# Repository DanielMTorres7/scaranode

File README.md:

# ScaraNode

Placa de nó de motor **Klipper** para braço SCARA: **RP2040-Zero** + **TMC2209** (NEMA 17) e/ou driver
externo **DM556** (NEMA 23), cada um com STEP/DIR/enable próprios. Face única, 76 × 64 mm, feita para fresar em casa.

| Projetista | Revisão | Data | Estado |
|---|---|---|---|
| Daniel M. Torres | v18 | 27/09/2026 | Validada: 124 pinos, ERC e paridade 0, DRC de cobre sem erro, nenhuma curva de trilha de 90° |

📘 **[Manual completo](docs/README.md)** · 📄 **[PDF](docs/ScaraNode-Manual-v18.pdf)** ·
🧾 **[Lista de materiais](docs/02-lista-de-materiais.md)** · 🔧 **[Montagem](docs/04-montagem.md)** ·
⚙️ **[Klipper](docs/07-firmware-klipper.md)** ·
🎛️ **[Painel web](https://danielmtorres7.github.io/scaranode/)** ([como usar](firmware/painel/README.md))

## Estrutura

```
hardware/     placa e esquemático KiCad (ScaraNode.kicad_pro / .kicad_pcb / .kicad_sch + bibliotecas do projeto)
production/   arquivos para fabricar: gerber/, furação, BOM.csv
firmware/     configuração Klipper de referência; painel/ = painel web de bancada + firmware MicroPython
docs/         manual (Markdown + PDF), imagens, histórico de revisões
```

## Editar a placa

Abra `hardware/ScaraNode.kicad_pro` no **KiCad 10**: esquemático (`ScaraNode.kicad_sch`) e placa
(`ScaraNode.kicad_pcb`). As tabelas de biblioteca do projeto (`sym-lib-table`, `fp-lib-table`) apontam para as
bibliotecas padrão do KiCad 10 e para as próprias: `ScaraNode.kicad_sym` (RP2040-Zero, StepStick, 74ACT245, diodos)
e `ScaraNode.pretty` (soquetes do RP2040-Zero e do StepStick). Os comandos para
regerar Gerber e furação estão em [docs/03-fabricacao.md](docs/03-fabricacao.md#arquivos-de-produção).

Placa e esquemático foram gerados e conferidos por uma ferramenta própria em Python, que não faz parte deste
repositório (a paridade placa × esquemático é verificada pelo `kicad-cli`; a sincronização pela interface —
"Atualizar placa a partir do esquemático" — não foi testada). Os arquivos KiCad são completos e editáveis sem ela.

## Licença

Hardware sob **CERN-OHL-S-2.0** (ver [`LICENSE`](LICENSE)). Fotos de terceiros em `docs/img/componentes/`
mantêm as licenças listadas em [`CREDITOS.md`](docs/img/componentes/CREDITOS.md).

## Créditos

Modelos 3D das peças: bibliotecas oficiais do KiCad. Fotos de componentes: Wikimedia Commons, com
autores e licenças em [`docs/img/componentes/CREDITOS.md`](docs/img/componentes/CREDITOS.md).

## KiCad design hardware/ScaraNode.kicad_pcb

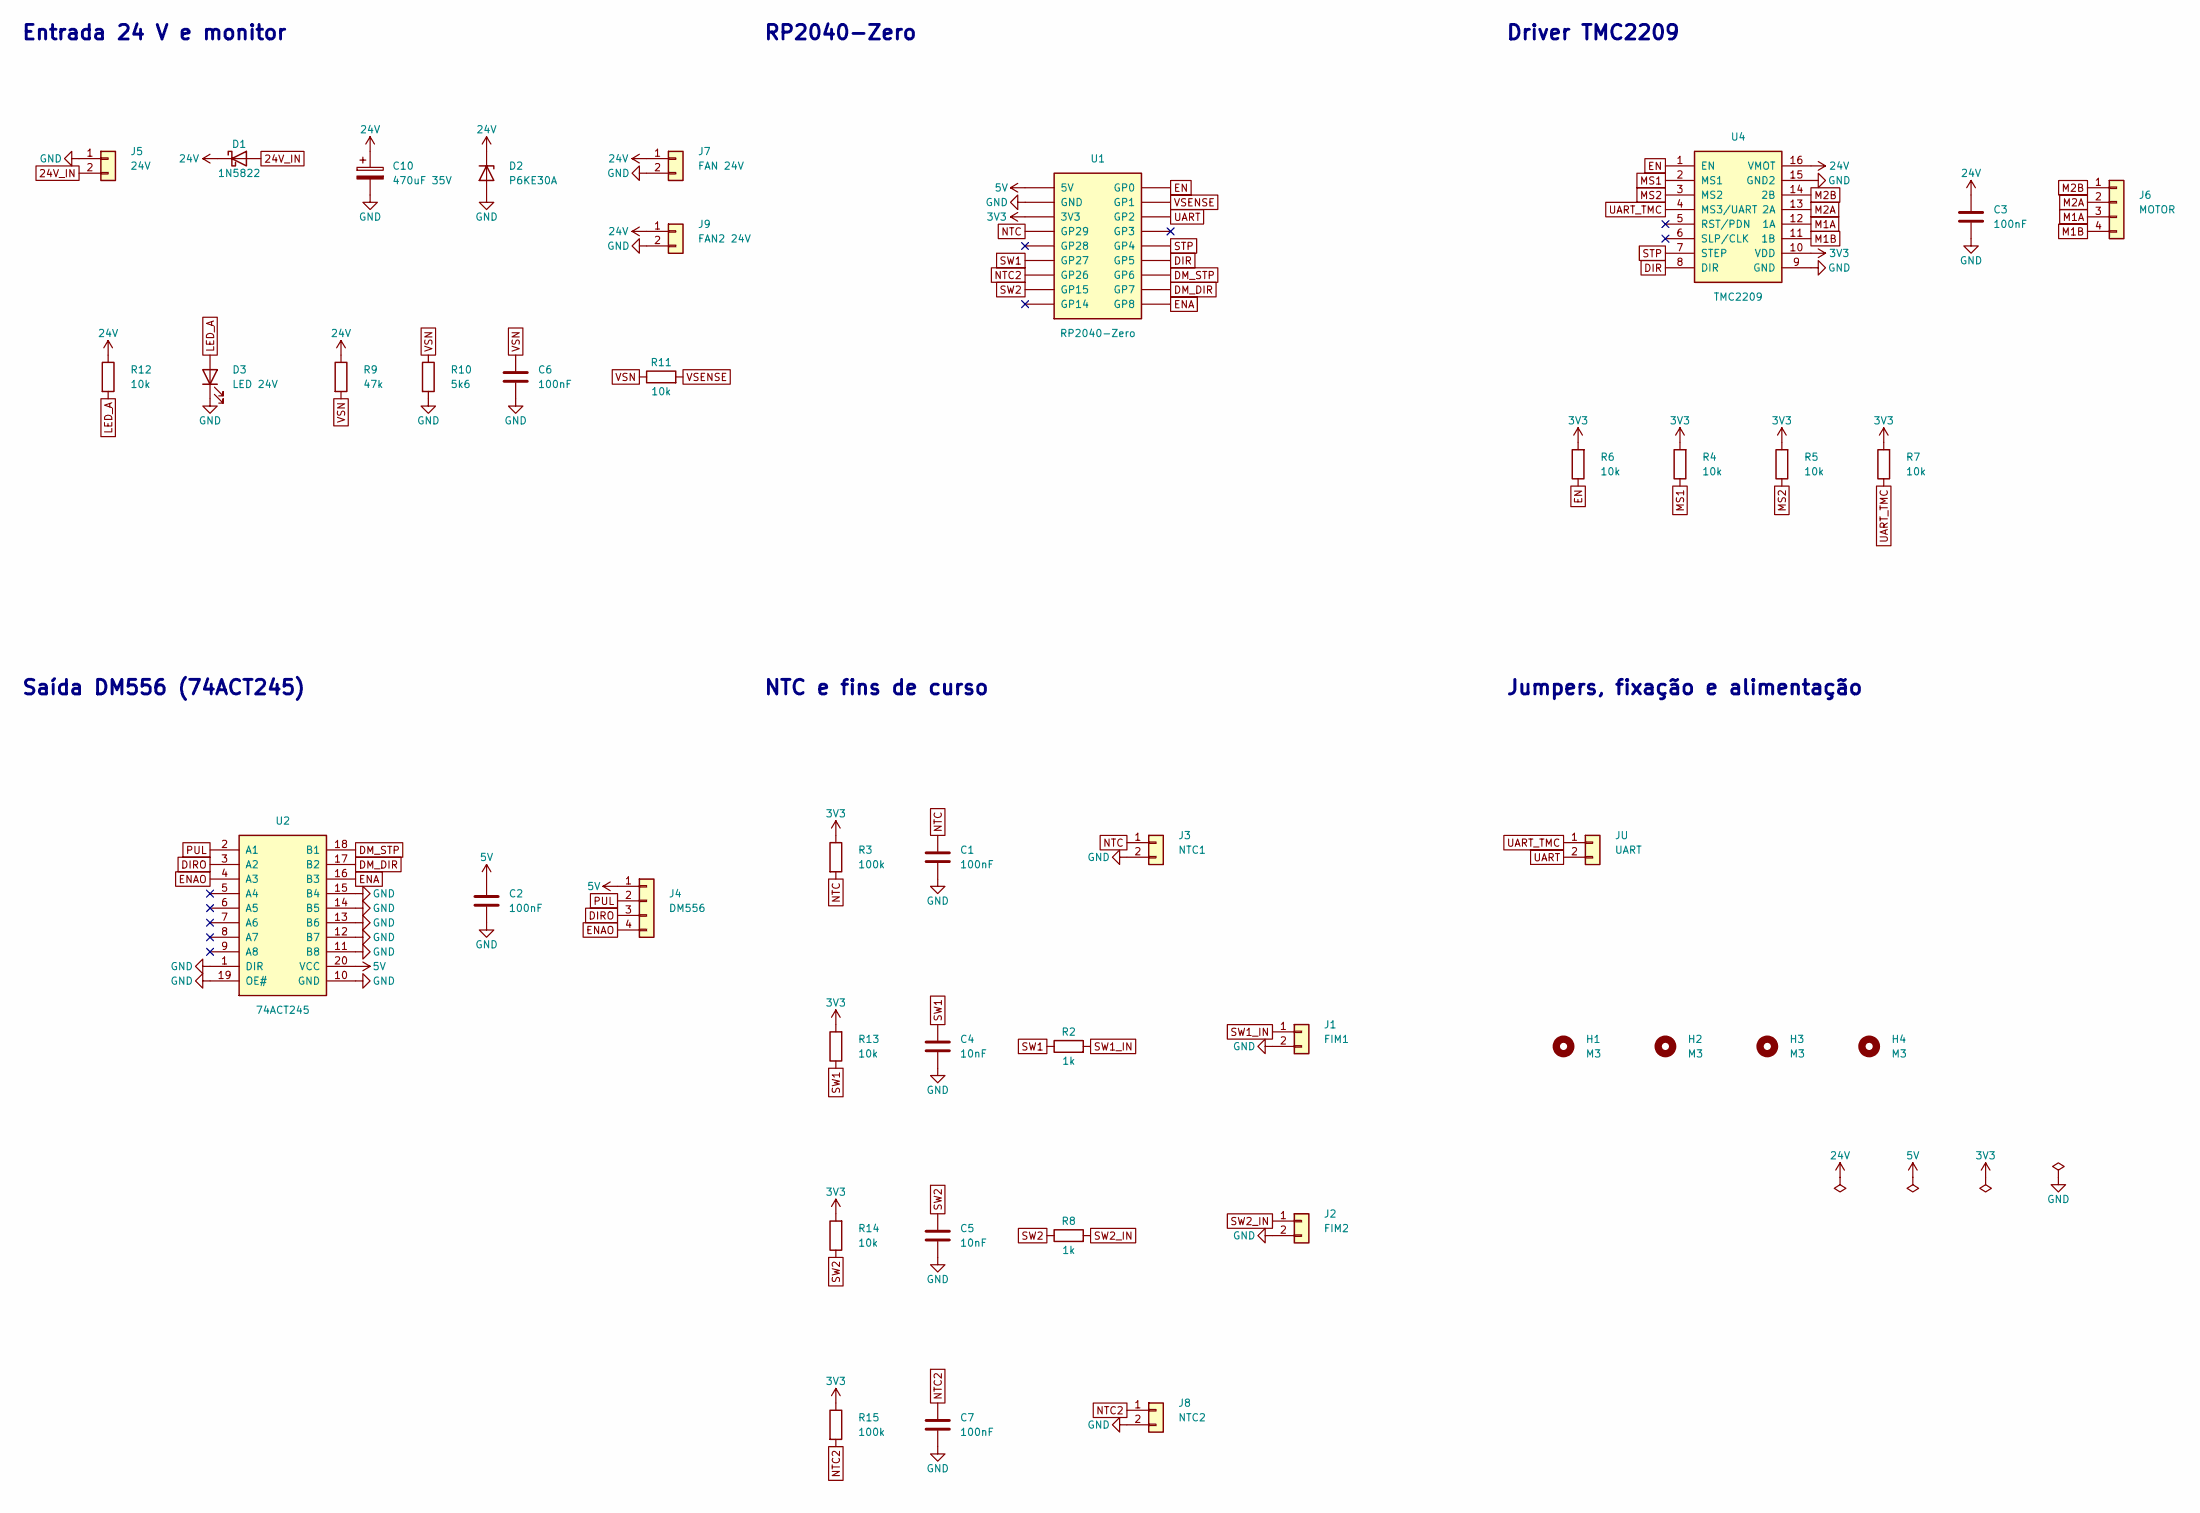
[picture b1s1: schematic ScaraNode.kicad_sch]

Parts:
C1, C2, C3, C6, C7: 100nF; C_Disc_D3.0mm_W1.6mm_P2.50mm
C4, C5: 10nF; C_Disc_D3.0mm_W1.6mm_P2.50mm
C10: 470uF 35V; CP_Radial_D10.0mm_P5.00mm
D1: 1N5822; D_DO-201AD_P12.70mm_Horizontal
D2: P6KE30A; D_DO-15_P10.16mm_Horizontal
D3: LED 24V; LED_D5.0mm
H1, H2, H3, H4: M3; MountingHole_3.2mm_M3
J1: FIM1; JST_XH_B2B-XH-A_1x02_P2.50mm_Vertical
J2: FIM2; JST_XH_B2B-XH-A_1x02_P2.50mm_Vertical
J3: NTC1; JST_XH_B2B-XH-A_1x02_P2.50mm_Vertical
J4: DM556; JST_XH_B4B-XH-A_1x04_P2.50mm_Vertical
J5: 24V; PhoenixContact_MSTBA_2,5_2-G-5,08_1x02_P5.08mm_Horizontal
J6: MOTOR; PhoenixContact_MSTBVA_2,5_4-G-5,08_1x04_P5.08mm_Vertical
J7: FAN 24V; JST_XH_B2B-XH-A_1x02_P2.50mm_Vertical
J8: NTC2; JST_XH_B2B-XH-A_1x02_P2.50mm_Vertical
J9: FAN2 24V; JST_XH_B2B-XH-A_1x02_P2.50mm_Vertical
JU: UART; PinHeader_1x02_P2.54mm_Vertical
R2, R8: 1k; R_Axial_DIN0207_L6.3mm_D2.5mm_P10.16mm_Horizontal
R3, R15: 100k; R_Axial_DIN0207_L6.3mm_D2.5mm_P10.16mm_Horizontal
R4, R5, R6, R7, R11, R12, R13, R14: 10k; R_Axial_DIN0207_L6.3mm_D2.5mm_P10.16mm_Horizontal
R9: 47k; R_Axial_DIN0207_L6.3mm_D2.5mm_P10.16mm_Horizontal
R10: 5k6; R_Axial_DIN0207_L6.3mm_D2.5mm_P10.16mm_Horizontal
U1: RP2040-Zero; RP2040-Zero_Socket
U2: 74ACT245; DIP-20_W7.62mm_Socket_LongPads
U4: TMC2209; StepStick_Socket

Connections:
3V3: R3.1, R4.2, R5.2, R6.2, R7.2, R13.2, R14.2, R15.1, U1.3V3, U4.10 (VDD)
5V: C2.1, J4.1, U1.5V, U2.20 (VCC)
24V: C3.1, C10.1, D1.1 (K), D2.1 (K), J7.1, J9.1, R9.1, R12.1, U4.16 (VMOT)
24V_IN: D1.2 (A), J5.2
DIR: U1.GP5, U4.8 (DIR)
DIRO: J4.3, U2.3 (A2)
DM_DIR: U1.GP7, U2.17 (B2)
DM_STP: U1.GP6, U2.18 (B1)
EN: R6.1, U1.GP0, U4.1 (EN)
ENA: U1.GP8, U2.16 (B3)
ENAO: J4.4, U2.4 (A3)
GND: C1.2, C2.2, C3.2, C4.2, C5.2, C6.2, C7.2, C10.2, D2.2 (A), D3.1 (K), J1.2, J2.2, J3.2, J5.1, J7.2, J8.2, J9.2, R10.2, U1.GND, U2.1 (DIR), U2.10 (GND), U2.11 (B8), U2.12 (B7), U2.13 (B6), U2.14 (B5), U2.15 (B4), U2.19 (OE#), U4.9 (GND), U4.15 (GND2)
LED_A: D3.2 (A), R12.2
M1A: J6.3, U4.12 (1A)
M1B: J6.4, U4.11 (1B)
M2A: J6.2, U4.13 (2A)
M2B: J6.1, U4.14 (2B)
MS1: R4.1, U4.2 (MS1)
MS2: R5.1, U4.3 (MS2)
NTC: C1.1, J3.1, R3.2, U1.GP29
NTC2: C7.1, J8.1, R15.2, U1.GP26
PUL: J4.2, U2.2 (A1)
STP: U1.GP4, U4.7 (STEP)
SW1: C4.1, R2.1, R13.1, U1.GP27
SW1_IN: J1.1, R2.2
SW2: C5.1, R8.1, R14.1, U1.GP15
SW2_IN: J2.1, R8.2
UART: JU.2, U1.GP2
UART_TMC: JU.1, R7.1, U4.4 (MS3/UART)
VSENSE: R11.2, U1.GP1
VSN: C6.1, R9.2, R10.1, R11.1

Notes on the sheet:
Entrada 24 V e monitor
RP2040-Zero
Driver TMC2209
Saída DM556 (74ACT245)
NTC e fins de curso
Jumpers, fixação e alimentação

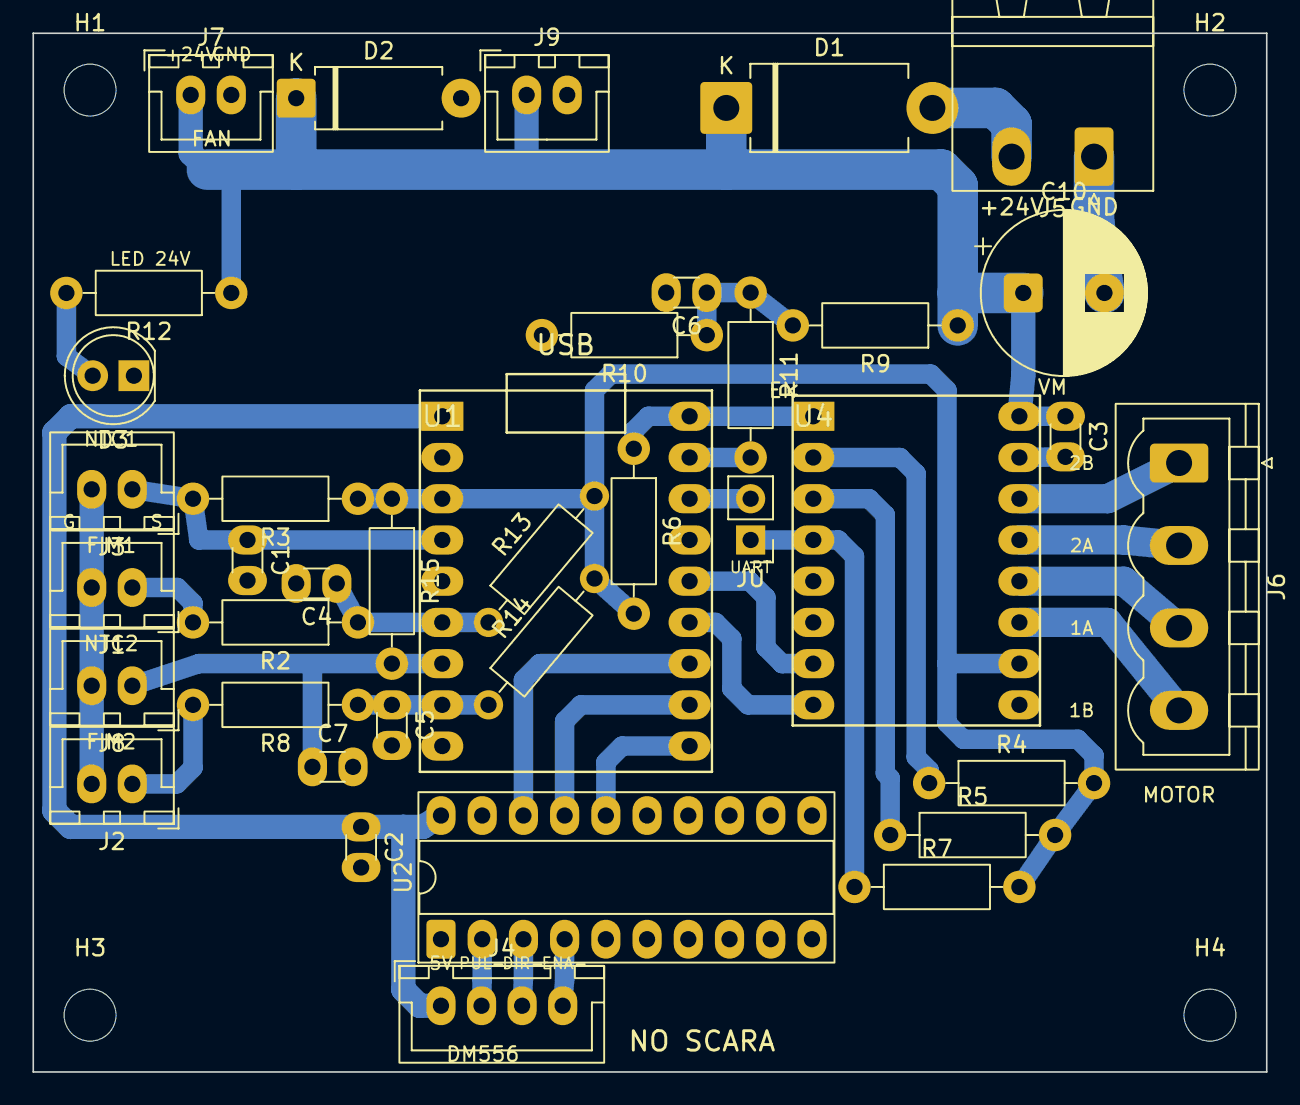
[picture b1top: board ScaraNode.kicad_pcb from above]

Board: 2 copper layers, 76.0 x 64.0 mm, 42 parts (0 on the bottom side), 31 nets.

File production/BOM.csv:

Qtd;Referencias;Valor;Descricao
5;C1 C2 C3 C6 C7;100nF;Capacitor ceramico 100 nF 50 V, passo 2,5 mm
2;C4 C5;10nF;Capacitor ceramico 10 nF 50 V, passo 2,5 mm
1;C10;470uF 35V;Capacitor eletrolitico 470 uF 35 V, 10 mm de diametro, passo 5 mm (105 C)
1;D1;1N5822;Diodo Schottky 1N5822 3 A 40 V (DO-201AD) - polaridade 24 V
1;D3;LED 24V;"LED 5 mm (qualquer cor) - indica 24 V; o de 3 mm usa os mesmos furos"
1;D2;P6KE30A;TVS P6KE30A unidirecional (DO-15) - protecao 24 V
1;J5;24V;Conector plugavel 2EDG 2 vias 5,08 mm: macho 90 graus 2EDGRC-5.08-2P + plugue 2EDGK-5.08-2P
1;J4;DM556;Conector JST XH 4 vias 2,5 mm, vertical (B4B-XH-A + femea XHP-4 + 4 terminais): 5V, PUL-, DIR-, ENA-
1;J7;FAN 24V;Conector JST XH 2 vias 2,5 mm, vertical (B2B-XH-A + femea XHP-2 + 2 terminais)
1;J9;FAN2 24V;Conector JST XH 2 vias 2,5 mm, vertical (B2B-XH-A + femea XHP-2 + 2 terminais)
1;J1;FIM1;Conector JST XH 2 vias 2,5 mm, vertical (B2B-XH-A + femea XHP-2 + 2 terminais)
1;J2;FIM2;Conector JST XH 2 vias 2,5 mm, vertical (B2B-XH-A + femea XHP-2 + 2 terminais)
1;J6;MOTOR;Conector plugavel 2EDG 4 vias 5,08 mm: macho vertical 2EDGVC-5.08-4P + plugue 2EDGK-5.08-4P
1;J3;NTC1;Conector JST XH 2 vias 2,5 mm, vertical (B2B-XH-A + femea XHP-2 + 2 terminais)
1;J8;NTC2;Conector JST XH 2 vias 2,5 mm, vertical (B2B-XH-A + femea XHP-2 + 2 terminais)
1;JU;UART;Barra de pinos macho 1x2 2,54 mm + 1 jumper (fechado = UART do TMC2209 no GP2, pino 4 do soquete)
2;R3 R15;100k;Resistor 1/4 W 5%, deitado, furos a 10,16 mm
8;R4 R5 R6 R7 R11 R12 R13 R14;10k;Resistor 1/4 W 5%, deitado, furos a 10,16 mm
2;R2 R8;1k;Resistor 1/4 W 5%, deitado, furos a 10,16 mm
1;R9;47k;Resistor 1/4 W 5%, deitado, furos a 10,16 mm
1;R10;5k6;Resistor 1/4 W 5%, deitado, furos a 10,16 mm
1;U2;74ACT245;SN74ACT245N DIP-20 (74HCT245N tambem serve), vai no soquete DIP-20
1;U1;RP2040-Zero;Waveshare RP2040-Zero
1;U4;TMC2209;Modulo TMC2209 StepStick (so no no com NEMA17)
2;-;Barra fêmea 1x9 2,54 mm;Soquete do RP2040-Zero
2;-;Barra fêmea 1x8 2,54 mm;Soquete do TMC2209
1;-;Soquete DIP-20 300 mil (7,62 mm);Para o 74ACT245 (U2): o soquete e soldado, o CI encaixa
4;H1-H4;Parafuso M3 + espaçador;Fixação
2;-;NTC 100k B3950 (com fio);Temperatura dos motores, vão no J3 e no J8 (o J8 só com dois motores na placa)
2;-;Chave fim de curso (NA ou NF);Vão no J1/J2 (ligam o pino ao GND)
1;-;Fusível de lâmina 2 A 32 V DC (ATO ou mini);Na caixa de fusíveis central, um só para esta placa (docs/06)

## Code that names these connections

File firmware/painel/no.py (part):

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# A revisão da placa vem do placa.py (REV = "v17"), gravado pelo painel; sem ele, v17.
# config.json (comando "salva"): driver, TMC, fins de curso e o bloco "robo" do painel (eixos ligados nesta
# placa, reduções, limites, referência). Lido na partida: a placa já liga configurada, com os motores soltos.
# Pinos comuns: EN GP0 · VSENSE GP1 · ENA do DM556 GP8 (alto = habilitado) · FIM1 GP27 · FIM2 GP15 · NTC GP29
# v18 também tem o NTC2 (motor do DM556) no GP26.
# v14–v17: UART GP5 (fio até o pino 4 do módulo) · STEP GP6 · DIR GP7, que vão ao mesmo tempo para o
#          TMC (soquete) e para o 74ACT245 -> J4 (DM556).
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PIN_UART, PIN_STEP_TMC, PIN_DIR_TMC, PIN_STEP_DM, PIN_DIR_DM = PLACAS[REV if REV_OK else "v17"]
COMUM = PIN_STEP_TMC == PIN_STEP_DM     # STEP/DIR compartilhados: permite o modo "ambos"
PINOS = {"tmc": (PIN_STEP_TMC, PIN_DIR_TMC), "dm556": (PIN_STEP_DM, PIN_DIR_DM)}
PIN_EN, PIN_VS, PIN_ENA = 0, 1, 8
PIN_FIM1, PIN_FIM2 = 27, 15
PIN_NTC, PIN_NTC2 = 29, (26 if REV == "v18" else None)
PIN_LED = 16                # WS2812 do RP2040-Zero (GRB)
BAUD = 115200             # UART do TMC: ~1,2 ms por leitura de registrador
RSENSE = 0.110
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# ---------- estado ----------

en = Pin(PIN_EN, Pin.OUT, value=1)
ena = Pin(PIN_ENA, Pin.OUT, value=0)     # DM556 desabilitado até o painel pedir
dirp = None                              # DIR do driver em uso (_pinos)
vs = Pin(PIN_VS, Pin.IN)
fim = (Pin(PIN_FIM1, Pin.IN, Pin.PULL_UP), Pin(PIN_FIM2, Pin.IN, Pin.PULL_UP))
# ADC pelo Pin: pelo número do canal (ADC(3)) o MicroPython 1.29 deixa o pull-down do GPIO ligado,
# que carrega o divisor de 100k e fazia o NTC marcar ~60 °C no ar.
adc_ntc = ADC(Pin(PIN_NTC))
adc_ntc2 = ADC(Pin(PIN_NTC2)) if PIN_NTC2 is not None else None
adc_t = ADC(4)

cfg = {"run": 0.8, "hold": 0.4, "micro": 16, "modo": "stealth", "vthr": 0,
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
